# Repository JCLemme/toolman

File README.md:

# toolman
Lil baby computer for IT work

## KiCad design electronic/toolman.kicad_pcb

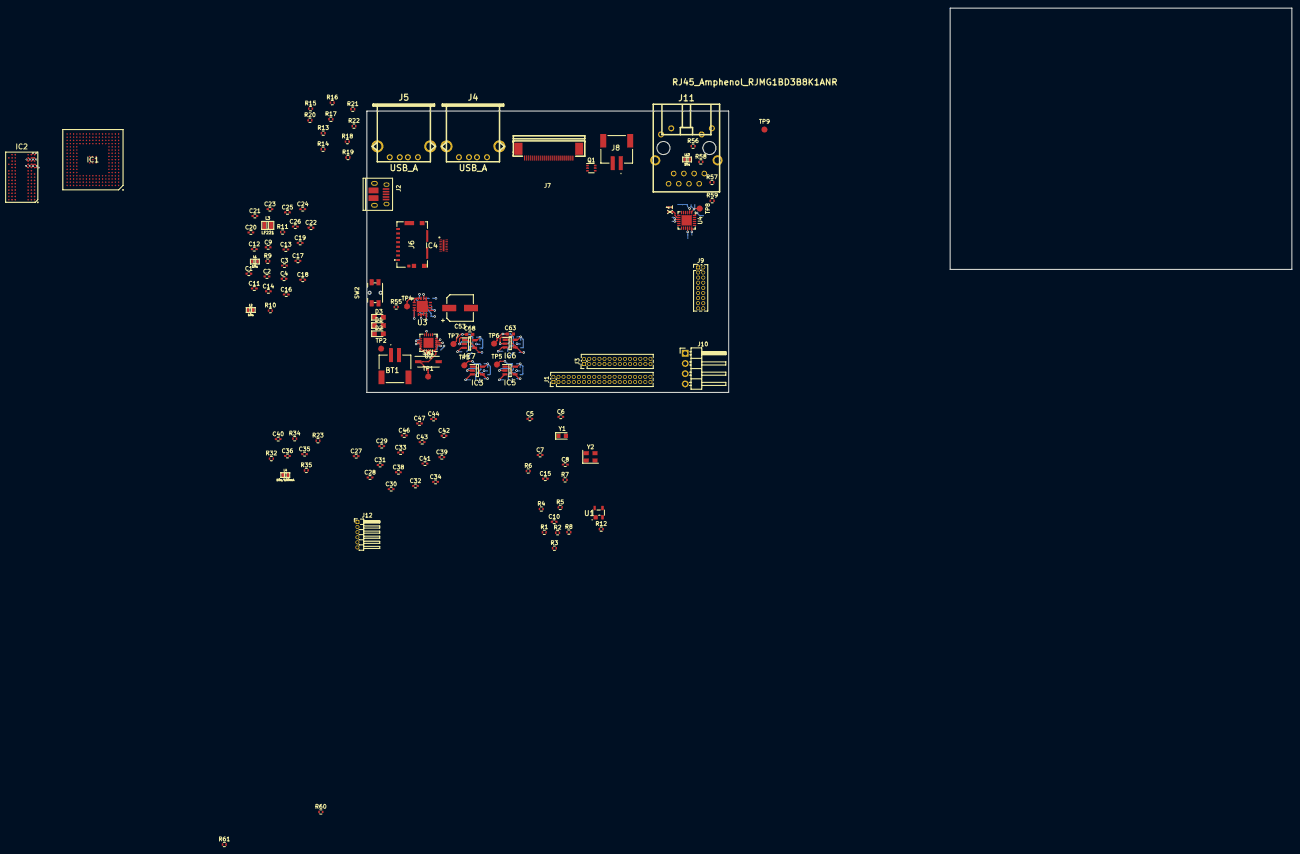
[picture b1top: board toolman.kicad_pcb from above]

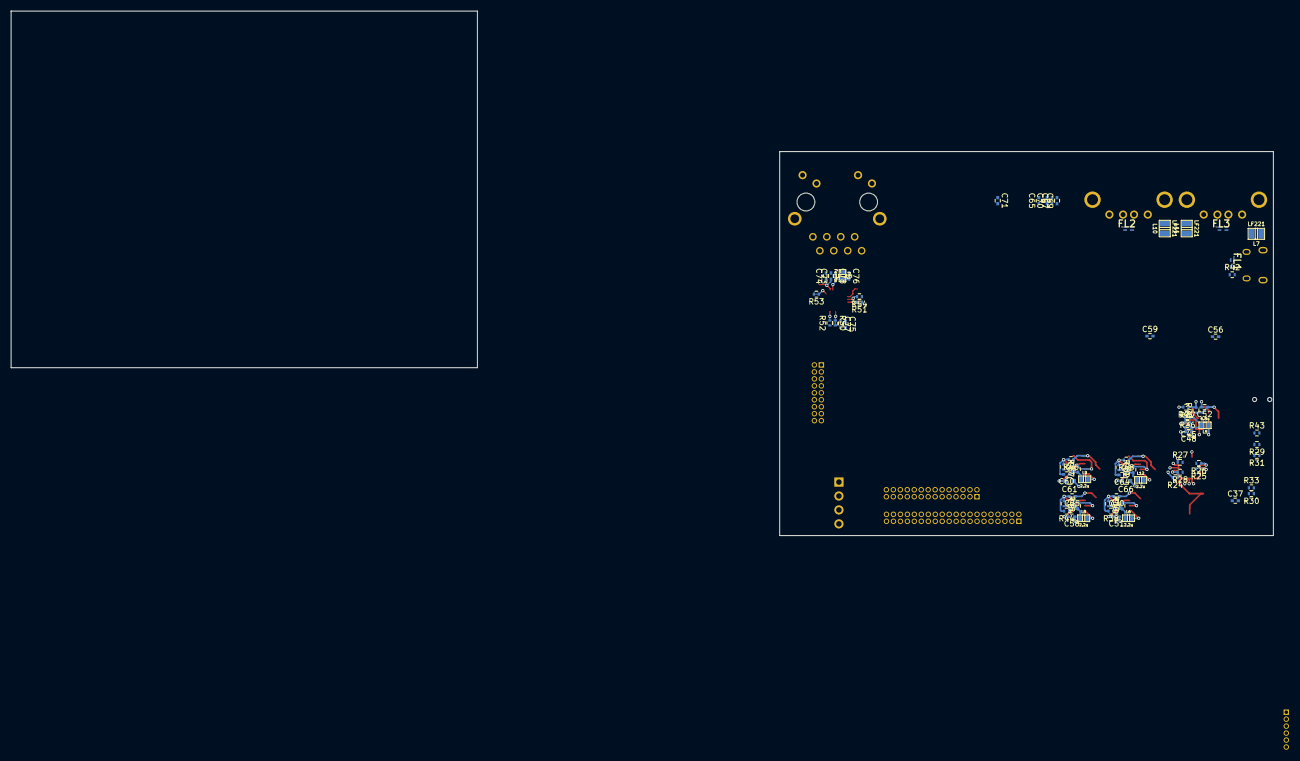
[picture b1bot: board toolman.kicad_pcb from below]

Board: 6 copper layers, 197 parts (69 on the bottom side), 212 nets.

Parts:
BT1: Battery_Cell; 1769
C1, C2, C3, C9, C11, C13, C16, C18, C20, C21, C22, C23, C24, C25, C26, C27, C28, C29, C30, C31, C32, C33, C34, C35, C38, C39, C40, C41, C42, C43, C44, C46, C47, C51, C58, C59: 100n; C_0402
C4, C12, C14, C17, C19, C36: 4.7u; C_0402
C5, C6: 22p; C_0402
C7, C8: 27p; C_0402
C10: 10n; C_0402
C15: 10p; C_0402
C37, C45, C49, C54, C56, C57, C62: 10u; C_0402
C48, C71, C74, C77, C78: 0.1u; C_0402
C50, C55, C60, C64: 15p; C_0402
C52, C73, C75, C76: 2.2u; C_0402
C53: 100u; CP_Elec_6.3x5.3
C61, C63, C66, C68: 47u 6.3v; C_0603
C65, C67, C69, C70: 1u; C_0402
D1: CHARGED; LED_0805
D2: CHARGING; LED_0805
D3: POWERON; LED_0805
FB1: Ferrite; inductor_smd_0603
FL1, FL2, FL3: LC DLP11S; DLP11S
IC1: AT91SAM9G25-CU-999; BGA217C80P17X17_1500X1500X140
IC2: W971GG6SB-25; BGA84C80P9X15_800X1250X120
IC3, IC5, IC6, IC7: NCP1529ASNT1G; SOT95P275X110-5N
IC4: CM1624-08DE; SON40P135X330X55-17N
J1: GPIO; Pin_Header_Straight_2x20_Pitch1.27mm
J2: USB_OTG; USB_Micro-B_10103594-0001LF
J3: HISPEED; Pin_Header_Straight_2x14_Pitch1.27mm
J4, J5: USB_A; conn_usb_A
J6: Micro_SD_Card; 1051620001
J7: DISPLAY; ER-CON25HB
J8: BACKLIGHT; 1769
J9: DEBUG; Pin_Header_Straight_2x09_Pitch1.27mm
J10: SERIAL; Pin_Header_Angled_1x04_Pitch2.54mm
J11: RJ45_Amphenol_RJMG1BD3B8K1ANR; rj45-wiznet-rb1-125bag1a
J12: KEYBOARD; Pin_Header_Angled_1x06_Pitch1.27mm
L1, L2, L13: 10u; inductor_smd_0603
L3, L7, L10, L11: LF221; inductor_smd_0805
L4: 10u/100mA; inductor_smd_0603
L5: 6.8u; inductor_smd_0603
L6, L8, L9, L12: 2.2u; inductor_smd_0603
Q1: Si1442DH; SOT-363_SC-70-6
R1, R2, R3, R4, R8, R26, R28, R39: 100k; R_0402
R5, R12, R55: 10k; R_0402
R6: 6.8k; R_0402
R7, R23, R50, R53, R57, R59: DNP; R_0402
R9, R10, R11: 1R; R_0402
R13, R16, R18, R21: 39 1%; R_0402
R14, R17, R19, R22: 0; R_0402
R15, R20: 27; R_0402
R24: 270k; R_0402
R25, R29, R30, R31, R43, R51, R52, R56, R58: 1k; R_0402
R27: 16k; R_0402
R32, R34: 1.5k; R_0402
R33: 1.4k; R_0402
R35: 1; R_0402
R36, R40: 1.87m; R_0402
R37: 340k; R_0402
R38, R41, R45: 200k; R_0402
R42, R60, R61: 47k; R_0402
R44: 147k 1%; R_0402
R46, R48: 1M 1%; R_0402
R47, R49: 220k 1%; R_0402
R54: 6.49k; R_0402
SW1: CUTOFF; SW_DIP_x1_W5.08mm_Slide_Copal_CHS-A
SW2: POWER; Panasonic_EVQPUL_EVQPUC
TP1: TEST_Vcharge; Measurement_Point_Round-SMD-Pad_Small
TP2: TEST_Vbatt; Measurement_Point_Round-SMD-Pad_Small
TP3: TEST_1.8v; Measurement_Point_Round-SMD-Pad_Small
TP4: TEST_5v; Measurement_Point_Round-SMD-Pad_Small
TP5: TEST_1.0v; Measurement_Point_Round-SMD-Pad_Small
TP6: TEST_3.3v; Measurement_Point_Round-SMD-Pad_Small
TP7: TEST_Vbackup; Measurement_Point_Round-SMD-Pad_Small
TP8: TEST_1.2v; Measurement_Point_Round-SMD-Pad_Small
TP9: TEST_LED; Measurement_Point_Round-SMD-Pad_Small
U1: CAT811TTBI-GT3; 4-PIN-SOT-143(BI-SUFFIX-CASE-527AF)
U2: MCP73871; QFN-20-1EP_4x4mm_Pitch0.5mm
U3: TPS61090; QFN65P400X400X100-17N
U4: KSZ8081RND; QFN-24-1EP_4x4mm_Pitch0.5mm
X1: ECS1612MV (50m); ECS1612MV250CNTR
Y1: ABS06-127-32.768kHz; Crystal_SMD_TXC_9HT11-2pin_2.0x1.2mm_HandSoldering
Y2: ECX33Q (12m); Crystal_SMD_EuroQuartz_MT-4pin_3.2x2.5mm

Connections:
+1V0: C1.1, C2.1, C3.1, C4.1, C16.2, C54.1, C55.1, IC1.H14, IC1.K8, IC1.K9, IC1.T17, L2.1, L8.1, R44.1, TP5.1
+1V8: C22.1, C24.1, C26.1, C27.2, C28.1, C29.2, C30.1, C31.2, C32.1, C33.2, C34.1, C38.2, C39.1, C41.2, C42.1, C43.2, C44.1, C46.2, C47.1, C49.1, C50.1, IC1.D10, IC1.D13, IC1.F14, IC2.A1, IC2.A9, IC2.C1, IC2.C3, IC2.C7, IC2.C9, IC2.E1, IC2.E9, IC2.G1, IC2.G3, IC2.G7, IC2.G9, IC2.J1, IC2.J9, IC2.M9, IC2.R1, L4.1, L6.1, R23.2, R38.1, TP3.1
+3V3: C11.1, C14.1, C21.1, C23.1, C25.1, C51.2, C56.2, C57.1, C58.2, C59.2, C60.1, C63.1, C71.2, C75.1, C77.1, FB1.1, IC1.A4, IC1.H4, IC1.J14, IC1.K14, IC1.P7, IC1.U16, IC3.1, IC3.4, IC4.12, IC5.1, IC5.4, J1.1, J3.1, J3.28, J6.4, J7.6, J7.11, J7.12, J7.14, J7.23, J8.1, J9.4, J12.6, L1.1, L3.1, L9.1, R1.2, R2.2, R4.2, R5.2, R7.1, R7.2, R8.2, R12.2, R42.1, R46.1, R51.1, R52.1, R56.1, R57.1, R57.2, R58.1, R59.1, R60.1, R61.1, TP6.1, U1.4, U4.14, X1.1, X1.4
+5V: C52.1, C53.1, C61.2, IC6.1, IC6.4, J1.2, R40.1, R43.2, TP4.1, U3.1, U3.15, U3.16
+BATT: BT1.1, C37.2, R30.2, TP2.1, U2.14, U2.15, U2.16
/A2: IC1.H15, IC2.M8
/A3: IC1.H17, IC2.M3
/A4: IC1.G17, IC2.M7
/A5: IC1.G16, IC2.N2
/A6: IC1.F17, IC2.N8
/A7: IC1.E17, IC2.N3
/A8: IC1.F16, IC2.N7
/A9: IC1.G15, IC2.P2
/A10: IC1.G14, IC2.P8
/A11: IC1.F15, IC2.P3
/A13: IC1.C17, IC2.P7
/A14: IC1.E16, IC2.R2
/A16: IC1.C16, IC2.L2
/A17: IC1.B17, IC2.L3
/A18: IC1.E15, IC2.L1
/BATTVOLT: IC1.B1, R30.1, R33.2
/BMS: IC1.P9, J9.13, R4.1
/CASn: IC1.C10, IC2.L7
/CHARGED: IC1.F4, R29.2, U2.7
/CHARGING: IC1.E2, R31.2, U2.8
/CPU_NRST: C10.1, IC1.P10, J9.15, J10.2, J12.2, R5.1, R53.1, R53.2, U1.2, U4.24
/CPU_NTRST: IC1.T11, J9.16
/CPU_SHDN: IC1.D8, J9.18, U3.11
/CPU_WKUP: IC1.A7, J9.14, R55.1, SW2.1
/D0: IC1.D14, IC2.G8
/D1: IC1.D15, IC2.G2
/D2: IC1.A16, IC2.H7
/D3: IC1.B16, IC2.H3
/D4: IC1.A17, IC2.H1
/D5: IC1.B15, IC2.H9
/D6: IC1.C14, IC2.F1
/D7: IC1.B14, IC2.F9
/D8: IC1.A15, IC2.C8
/D9: IC1.C15, IC2.C2
/D10: IC1.D12, IC2.D7
/D11: IC1.C13, IC2.D3
/D12: IC1.A14, IC2.D1
/D13: IC1.B13, IC2.D9
/D14: IC1.A13, IC2.B1
/D15: IC1.C12, IC2.B9
/DDR_CLK_N: IC1.C11, IC2.K8
/DDR_CLK_P: IC1.D11, IC2.J8
/DDR_VREF: C35.1, C40.2, IC2.J2, R32.1, R34.2
/DEVICE_M: FL1.4, R21.1, R22.1
/DEVICE_P: FL1.3, R16.1, R17.1
/DQM0: IC1.A10, IC2.F3
/DQM1: IC1.B10, IC2.B3
/DQS0: IC1.A11, IC2.F7
/DQS1: IC1.A9, IC2.B7
/HFSDMA: IC1.T15, R21.2
/HFSDMB: IC1.P16, R18.2
/HFSDMC: IC1.M17, R20.2
/HFSDPA: IC1.T14, R16.2
/HFSDPB: IC1.R16, R13.2
/HFSDPC: IC1.L17, R15.2
/HHSDMA: IC1.U15, R22.2
/HHSDMB: IC1.P17, R19.2
/HHSDPA: IC1.U14, R17.2
/HHSDPB: IC1.R17, R14.2
/HOST_M: FL2.4, R18.1, R19.1
/HOST_P: FL2.3, R13.1, R14.1
/JTAGSEL: IC1.D7, J9.11, R3.1
/LHOST_M: FL3.4, R20.1
/LHOST_P: FL3.3, R15.1
/LOWBATTERY: IC1.F3, U3.12
/NCS1: IC1.B8, IC2.L8
/PA0_TXD0: IC1.L3, J1.21
/PA1_RXD0: IC1.P1, J1.25
/PA2_RTS0: IC1.L4, J1.22
/PA3_CTS0: IC1.N4, J1.24
/PA4_SCK0: IC1.T3, J1.26
/PA5_TXD1: IC1.R1, J1.29
/PA6_RXD1: IC1.R4, J1.31
/PA7_TXD2: IC1.R3, J1.30
/PA8_RXD2: IC1.P4, J1.32
/PA9_DRDX: IC1.U3, J10.3
/PA10_DTXD: IC1.T1, J10.4
/PA12_SPI0_MOSI: IC1.T2, J7.22
/PA13_SPI0_SPCK: IC1.T4, J7.24
/PA14_SPI0_NPCS0: IC1.U2, J7.9
/PA15_MCI0_DA0: IC1.U4, IC4.2
/PA16_MCI0_CDA: IC1.P5, IC4.6
/PA17_MCI0_CK: IC1.R5, IC4.3
/PA18_MCI0_DA1: IC1.U5, IC4.1
/PA19_MCI0_DA2: IC1.T5, IC4.8
/PA20_MCI0_DA3: IC1.U6, IC4.7
/PA21_TIOA0: IC1.T6, J3.9
/PA22_TIOA1: IC1.R6, J3.13
/PA23_TIOA2: IC1.U7, J3.17
/PA24_TCLK0: IC1.T7, J3.8
/PA25_TCLK1: IC1.T8, J3.12
/PA26_TCLK2: IC1.R7, J3.16
/PA27_TIOB0: IC1.P8, J3.5
/PA28_TIOB1: IC1.U8, J3.4
/PA29_KEY_INT: IC1.R9, J12.5
/PA30_TWD0: IC1.R8, J12.3, R60.2
/PA31_TWCK0: IC1.U9, J12.4, R61.2
/PB0_ERX0: IC1.D3, U4.13
/PB1_ERX1: IC1.D4, U4.12
/PB2_ERXER: IC1.D2, U4.17
/PB3_ERXDV: IC1.E4, U4.15
/PB4_ETXCK: IC1.D1, R50.1, R50.2, U4.16
/PB7_ETXEN: IC1.C2, U4.19
/PB9_ETX0: IC1.C1, U4.20
/PB10_ETX1: IC1.B2, U4.21
/PB12_DISPLAY_RESET: IC1.B4, J7.13
/PB13_DISPLAY_BACKLIGHT: IC1.A2, Q1.3
/PB14_DISPLAY_ADDRESS: IC1.C4, J7.21
/PB15_AD4: IC1.C3, J1.20
/PB16_AD5: IC1.A1, J1.28
/PC3: IC1.H2, J1.3
/PC4: IC1.E1, J1.5
/PC5: IC1.G4, J1.7
/PC6: IC1.F2, J1.9
/PC7: IC1.F1, J1.11
/PC8: IC1.G1, J1.13
/PC9: IC1.G3, J1.15
/PC10: IC1.G2, J1.4
/PC11: IC1.H3, J1.6
/PC12: IC1.J3, J1.8
/PC13: IC1.L2, J1.10
/PC14: IC1.H1, J1.12
/PC15: IC1.J2, J1.14
/PC16: IC1.J1, J1.16
/PC17: IC1.L1, J1.18
/PC18_PWM0: IC1.K2, J3.21
/PC19_PWM1: IC1.N3, J3.25
/PC20_PWM2: IC1.K1, J3.20
/PC21_PWM3: IC1.M3, J3.24
/PC22_TXD3: IC1.P3, J1.35
/PC23_RXD3: IC1.J4, J1.39
/PC24_RTS3: IC1.K3, J1.36
/PC25_CTS3: IC1.M2, J1.38
/PC26_SCK3: IC1.P2, J1.40
/RASn: IC1.B11, IC2.K7
/RTCK: IC1.R10, J9.12
/SDA10: IC1.C8, IC2.M2
/SDCKE: IC1.B12, IC2.K2
/TCK: IC1.U10, J9.1, R1.1
/TDI: IC1.T9, J9.9, R2.1
/TDO: IC1.T10, J9.3
/TMS: IC1.U11, J9.5, R8.1
/VBG: C15.2, IC1.U17, R6.2
/WEn: IC1.A12, IC2.K3
/XIN: C7.1, IC1.T12, Y2.1
/XIN32: C5.1, IC1.A6, Y1.1
/XOUT: C8.1, IC1.U12, Y2.3
/XOUT32: C6.1, IC1.A5, Y1.2
GND: BT1.2, C1.2, C2.2, C3.2, C4.2, C5.2, C6.2, C7.2, C8.2, C9.2, C10.2, C11.2, C12.2, C13.2, C14.2, C15.1, C16.1, C17.2, C18.2, C19.2, C20.2, C21.2, C22.2, C23.2, C24.2, C25.2, C26.2, C27.1, C28.2, C29.1, C30.2, C31.1, C32.2, C33.1, C34.2, C35.2, C36.2, C37.1, C38.1, C39.2, C41.1, C42.2, C43.1, C44.2, C45.2, C46.1, C47.2, C48.2, C49.2, C51.1, C52.2, C53.2, C54.2, C56.1, C57.2, C58.1, C59.1, C61.1, C62.2, C63.2, C65.2, C66.1, C68.2, C69.2, C70.2, C71.1, C73.2, C74.2, C75.2, C76.1, C77.2, C78.1, D3.1, IC1.B6, IC1.B7, IC1.D6, IC1.H8, IC1.H9, IC1.H10, IC1.J8, IC1.J9, IC1.J10, IC1.K10, IC1.M4, IC1.P6, IC1.T16, IC1.U13, IC2.A3, IC2.A7, IC2.B2, IC2.B8, IC2.D2, IC2.D8, IC2.E3, IC2.E7, IC2.F2, IC2.F8, IC2.H2, IC2.H8, IC2.J3, IC2.J7, IC2.K9, IC2.N1, IC2.P9, IC3.2, IC4.17, IC5.2, IC6.2, IC7.2, J1.19, J1.23, J1.27, J1.33, J1.34, J1.37, J2.5, J3.2, J3.3, J3.6, J3.7, J3.10, J3.11, J3.14, J3.15, J3.18, J3.19, J3.22, J3.23, J3.26, J3.27, J4.4, J5.4, J6.6, J6.9, J7.1, J7.7, J7.10, J7.25, J9.2, J9.10, J10.1, J12.1, L7.1, L10.1, L11.1, L13.1, Q1.4, R3.2, R6.1, R23.1, R25.2, R26.2, R27.2, R28.1, R32.2, R33.1, R37.2, R39.2, R41.2, R45.2, R47.2, R49.2, R54.1, R59.2, SW2.2, U1.1, U2.10, U2.11, U2.21, U3.5, U3.6, U3.7, U3.10, U3.13, U3.17, U4.22, U4.25, X1.2, Y2.2, Y2.4
unnamed: C9.1, IC1.T13, L1.2, R9.1
unnamed: C12.1, R9.2
unnamed: C13.1, IC1.R12, L2.2, R10.1
unnamed: C17.1, R10.2
unnamed: C18.1, IC1.C6, L3.2, R11.1
unnamed: C19.1, R11.2
unnamed: C36.1, R35.2
unnamed: C40.1, L4.2, R34.1, R35.1
unnamed: C50.2, IC3.5, R38.2, R39.1
unnamed: C55.2, IC5.5, R44.2, R45.1
unnamed: C60.2, IC6.5, R46.2, R47.1
unnamed: C64.2, IC7.5, R48.2, R49.1
unnamed: C65.1, J7.8
unnamed: C67.1, J7.4
unnamed: C67.2, J7.3
unnamed: C69.1, J7.2
unnamed: C70.1, J7.5
unnamed: C73.1, C74.1, TP8.1, U4.1
unnamed: C76.2, C78.2, FB1.2, U4.2
unnamed: D1.1, R29.1
unnamed: D2.1, R31.1
unnamed: D3.2, R43.1
unnamed: FL1.1, J2.2
unnamed: FL1.2, J2.3
unnamed: FL2.1, J4.2
unnamed: FL2.2, J4.3
unnamed: FL3.1, J5.2
unnamed: FL3.2, J5.3
unnamed: IC3.3, L6.2
unnamed: IC4.9, J6.1
unnamed: IC4.10, J6.2
unnamed: IC4.11, J6.3
unnamed: IC4.14, J6.5
unnamed: IC4.15, J6.7
unnamed: IC4.16, J6.8
unnamed: IC5.3, L8.2
unnamed: IC6.3, L9.2
unnamed: IC7.3, L12.2
unnamed: J2.4, R42.2
unnamed: J2.6, L7.2
unnamed: J8.2, Q1.1, Q1.2, Q1.5, Q1.6
unnamed: J11.13, L13.2
unnamed: L5.1, U3.3, U3.4
unnamed: R12.1, U1.3
unnamed: R24.1, R28.2, U2.2
unnamed: R25.1, U2.13
unnamed: R26.1, U2.12
unnamed: R27.1, U2.5
unnamed: R36.2, R37.1, U3.9
unnamed: R40.2, R41.1, U3.14
unnamed: R51.2, U4.10
unnamed: R52.2, U4.18
unnamed: R54.2, U4.9
unnamed: SW1.1, TP1.1, U2.1, U2.20
unnamed: U4.8, X1.3
VBUS: D1.2, D2.2, J2.1, J4.1, J5.1, R24.2, U2.3, U2.4, U2.9, U2.17, U2.18, U2.19
VEE: C20.1, C62.1, C64.1, C68.1, IC1.B5, J1.17, L12.1, R48.1, R55.2, TP7.1
VPP: C45.1, C48.1, C66.2, IC7.1, IC7.4, L5.2, R36.1, SW1.2, U3.8

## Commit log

2019-03-25 initial push
2019-03-30 bee gee aay
2019-04-01 this is hard
